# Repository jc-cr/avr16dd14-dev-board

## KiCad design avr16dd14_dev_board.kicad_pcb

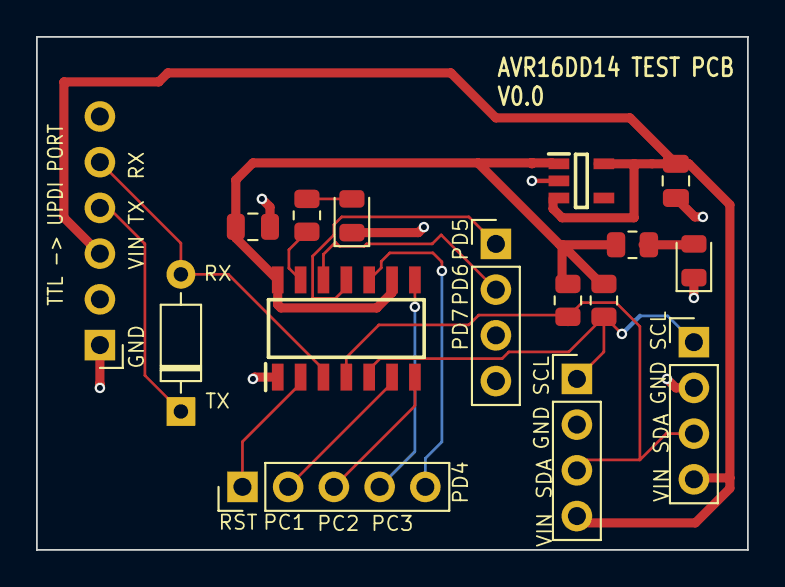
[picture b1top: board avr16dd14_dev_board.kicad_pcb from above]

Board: 2 copper layers, 39.5 x 28.5 mm, 16 parts (0 on the bottom side), 17 nets.

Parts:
C1, C2: 22uF; C_0805_2012Metric
D1, D2: LED; LED_0805_2012Metric
D3: BAT85; D_DO-35_SOD27_P7.62mm_Horizontal
IC1: AVR16DD14-I_SL; SOIC127P600X175-14N
IC2: ST730M33R; SOT95P280X145-5N
J1: Conn_01x06_Pin; PinHeader_1x06_P2.54mm_Horizontal
J2, J4, J5: Conn_01x04; PinHeader_1x04_P2.54mm_Vertical
J6: Conn_01x05; PinHeader_1x05_P2.54mm_Vertical
R2, R3: 1k; R_0805_2012Metric
R4, R5: 470; R_0805_2012Metric

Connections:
0: C1.1, C2.1, D1.1 (K), D2.1 (K), IC1.1 (GND), IC2.2 (GND), J1.1, J2.2, J4.2
/PC1: IC1.6 (PC1), J6.2
/PC2: IC1.7 (PC2), J6.3
/PC3: IC1.8 (PC3), J6.4
/PD4: IC1.10 (PD4), J6.5
/PD5: IC1.11 (PD5), J5.1
/PD6: IC1.12 (PD6), J5.2
/PD7: IC1.13 (PD7), J5.3, R5.2
/RESET: IC1.2 (PF6(~RESET)), J6.1
/RX: D3.2 (A), IC1.3 (PF7(UPDI)), J1.5
/SCL: IC1.5 (PA1(XTAL2)), J2.1, J4.1, R3.1
/SDA: IC1.4 (PA0(XTAL1)), J2.3, J4.3, R2.1
/TX: D3.1 (K), J1.4
/VDD: C1.2, IC1.9 (VDDIO2), IC1.14 (VDD), IC2.1 (VOUT), R2.2, R3.2, R4.2
/VIN: C2.2, IC2.3 (VIN), IC2.5 (EN), J1.3, J2.4, J4.4
unnamed: D1.2 (A), R4.1
unnamed: D2.2 (A), R5.1

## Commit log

2024-03-21 first
